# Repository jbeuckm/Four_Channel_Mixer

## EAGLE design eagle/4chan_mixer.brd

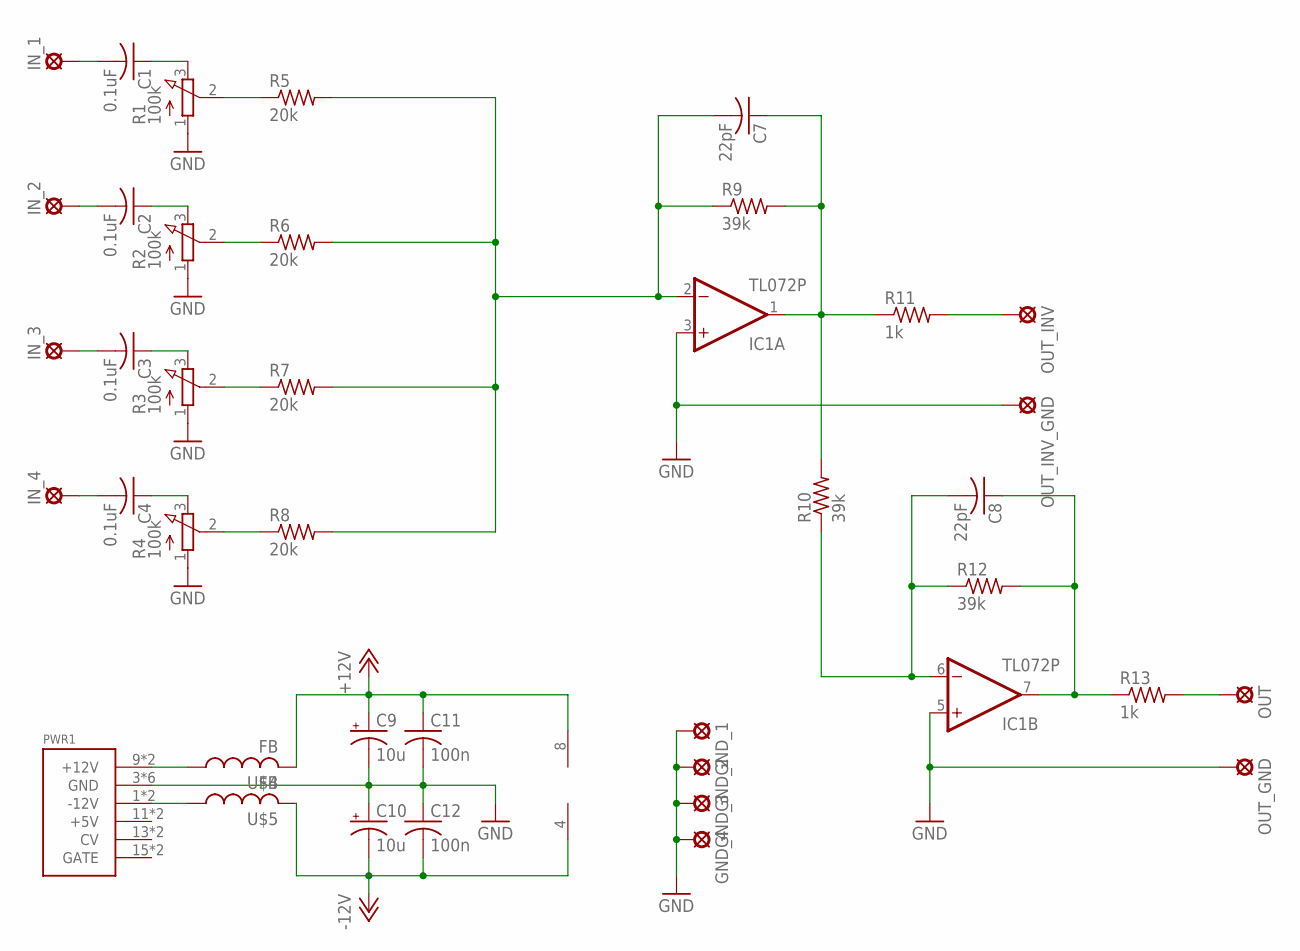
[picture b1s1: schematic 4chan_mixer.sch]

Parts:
C1, C2, C3, C4: 0.1uF; C050-030X075
C7, C8: 22pF; C050-030X075
C9, C10: 10u; B45181A
C11, C12: 100n; C050-024X044
GND_1, GND_2, GND_3, GND_4: LSP11
IC1: TL072P; DIL08
IN_1, IN_2, IN_3, IN_4: LSP11
OUT: LSP11
OUT_GND: LSP11
OUT_INV: LSP11
OUT_INV_GND: LSP11
PWR1: POWER; POWER_16
R1, R2, R3, R4: 100k; 3RP/1610N
R5, R6, R7, R8: 20k; 0207/7
R9, R10, R12: 39k; 0207/7
R11, R13: 1k; 0207/7
U$4, U$5: FB

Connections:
+12V: C9.+, C11.1, IC1.8 (V+), U$4.P$2 (2)
-12V: C10.-, C12.2, IC1.4 (V-), U$5.P$2 (2)
GND: C9.-, C10.+, C11.2, C12.1, GND_1.MP, GND_2.MP, GND_3.MP, GND_4.MP, IC1.3 (+IN), IC1.5 (+IN), OUT_GND.MP, OUT_INV_GND.MP, PWR1.3 (GND), PWR1.4 (GND), PWR1.5 (GND), PWR1.6 (GND), PWR1.7 (GND), PWR1.8 (GND), R1.1 (A), R2.1 (A), R3.1 (A), R4.1 (A)
unnamed: C2.2, IN_2.MP
unnamed: C2.1, R2.3 (E)
unnamed: R2.2 (S), R6.1
unnamed: C8.2, IC1.6 (-IN), R10.1, R12.1
unnamed: C8.1, IC1.7 (OUT), R12.2, R13.1
unnamed: PWR1.9 (+12V), PWR1.10 (+12V), U$4.P$1 (1)
unnamed: C3.2, IN_3.MP
unnamed: C3.1, R3.3 (E)
unnamed: R3.2 (S), R7.1
unnamed: C4.2, IN_4.MP
unnamed: C4.1, R4.3 (E)
unnamed: R4.2 (S), R8.1
unnamed: C1.2, IN_1.MP
unnamed: C1.1, R1.3 (E)
unnamed: R1.2 (S), R5.1
unnamed: C7.2, IC1.2 (-IN), R5.2, R6.2, R7.2, R8.2, R9.1
unnamed: C7.1, IC1.1 (OUT), R9.2, R10.2, R11.1
unnamed: OUT_INV.MP, R11.2
unnamed: OUT.MP, R13.2
unnamed: PWR1.1 (-12V), PWR1.2 (-12V), U$5.P$1 (1)

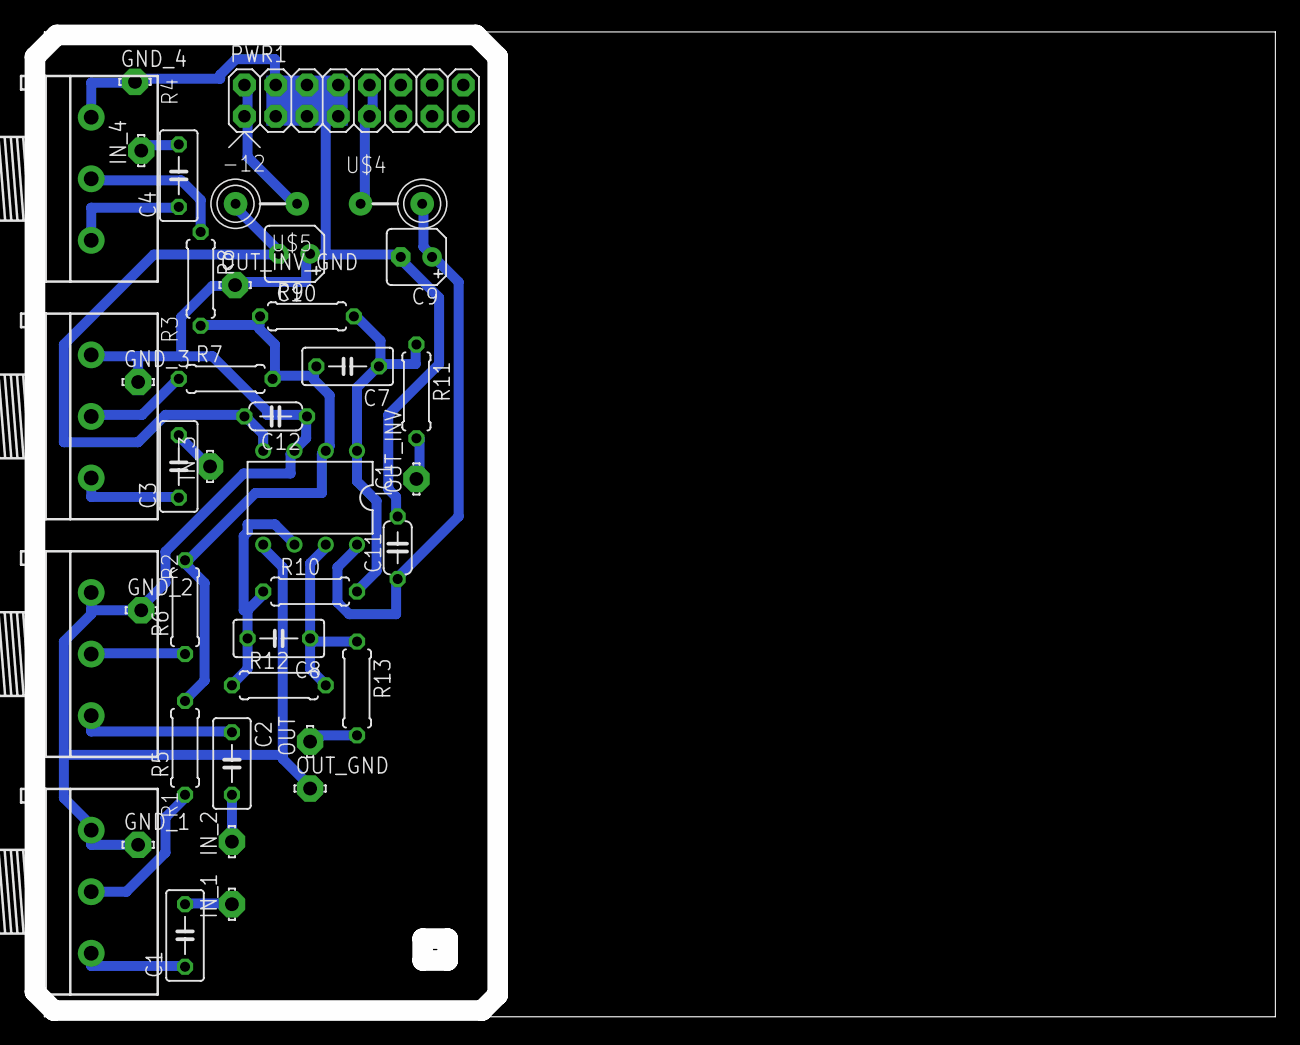
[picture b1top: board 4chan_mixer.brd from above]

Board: 2 copper layers, 100.8 x 80.0 mm, 39 parts (0 on the bottom side), 23 nets.

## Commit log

2015-12-01 grounds and cutout path for cnc
2015-12-01 panel design adjusted to new pcb
2016-03-24 now with ferrite bead filters and decouple caps closer to opamp
